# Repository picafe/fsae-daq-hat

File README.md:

# FSAE Pi HAT
## What this project is

This project is a revision 2.5 of the Raspberry Pi DAQ (data acquisition) HAT for Western Formula Racing FSAE. It consolidates the features still needed from the failed rev 2 boards into a single HAT: a 24 V → 5 V buck converter to power the Pi, input protection on the car rail, CAN transceiver + controller, static PoE injection control, and RTC with coin cell for the Pi 4B.

## Why I made it

A few months ago, I and another WFR team member tested and diagnosed a cause of catastrophic failure of the rev 2 DAQ HAT using voltage injection and a thermal camera. Although rev 3 was planned, and I am still working on it with help from others, the current failed rev 2 PCBs are still being partially used for their features that still function. This aims to be a quick revision that consolidates some of the features, while being cheap to manufacture. When revision 3 is finished, these boards can act as a backup.

The buck converter is one of the essential parts of the hat. Existing modules cut too many corners to be reliable, especially at 3A peak current. Currently, the buck coverter on the Rev 2 board is blown up. 

Rev 2 also included a boost converter to boost 20V USB-C PD to 24 V for injecting PoE for the base station antenna, and for ease of powering during testing. Since this is at a lower current, I decided to use a modified MT3608 boost converter and a PDC004 USB-C PD trigger on a separate PCB for ease of design and cost.

## Pictures

### 3D

### Schematic

**[View schematic online (KiCanvas)](https://kicanvas.org/?repo=https%3A%2F%2Fgithub.com%2Fpicafe%2Ffsae-daq-hat%2Fblob%2Fmain%2Ffsae-pihat%2Ffsae-pihat.kicad_sch)**

### PCB (KiCad)

**[View PCB online (KiCanvas)](https://kicanvas.org/?repo=https%3A%2F%2Fgithub.com%2Fpicafe%2Ffsae-daq-hat%2Fblob%2Fmain%2Ffsae-pihat%2Ffsae-pihat.kicad_pcb)**

### Wiring (off-board)

The 20 V USB-C PD → 24 V boost path is **not** on this HAT. It is implemented on the companion [USB boost/PD module](./fsae-pihat-usbmod/README.md), wired to the **J3** pads on the HAT.

```text
HAT J3 pads (no header installed)
    │  wire
    ▼
Deutsch connector
    │  wire
    ▼
USB-C PD breakout (MT3608 + PDC004)
```
The 2 main power devices source power from different sources using power OR-ing with schottky barrier diodes. 

The buck converter is powered by 24V from the car rail or the 20V USB-C PD (to reduce strain on the boost converter and to keep less ripple on the 5 V rail).
The PoE injector is powered by 24V from the car rail or the 24v boost converter.

A jumper on the **24 V car** input (JP2) can disable the car rail without unplugging the Deutsch connector, to preserve the car battery during bench testing. This MUST be populated to enable the car rail with a high current 0.1" pitch jumper. There is also a CAN termination jumper (JP1) to enable or disable 120Ω termination on the CAN bus.

## USB boost / PD module

The MT3608 boost and PDC004 USB-C PD trigger are on a separate PCB. Schematics, layout, images, and BOM for that board are in **[fsae-pihat-usbmod/README.md](./fsae-pihat-usbmod/README.md)**.

## Bill of materials (Pi HAT)

### JLCPCB SMT assembly

| Refs | Qty | Description | LCSC | Unit (USD) | Min | Ext. @ min (USD) |
| --- | ---: | --- | --- | ---: | ---: | ---: |
| C1, C2, C3 | 3 | 4.7 µF ±10% 50 V X7R ceramic, 1206 | [C29823](https://www.lcsc.com/product-detail/C29823.html) | $0.0426 | 10 | $0.43 |
| C10, C9 | 2 | 30 pF ±5% 50 V C0G ceramic, 0402 | [C1570](https://www.lcsc.com/product-detail/C1570.html) | $0.0013 | 100 | $0.13 |
| C11, C12 | 2 | 100 nF ±10% 50 V X7R ceramic, 0603 | [C14663](https://www.lcsc.com/product-detail/C14663.html) | $0.0031 | 100 | $0.31 |
| C4 | 1 | 10 nF ±10% 50 V X7R ceramic, 0805 | [C1710](https://www.lcsc.com/product-detail/C1710.html) | $0.0072 | 50 | $0.36 |
| C5 | 1 | 22 pF ±5% 50 V C0G ceramic, 0402 | [C1555](https://www.lcsc.com/product-detail/C1555.html) | $0.0014 | 100 | $0.14 |
| C6 | 1 | 330 µF ±20% 6.3 V tantalum, 7.3×4.3 mm SMD (6TPE330MAP) | [C79112](https://www.lcsc.com/product-detail/C79112.html) | $0.6851 | 1 | $0.69 |
| C7 | 1 | 100 nF ±10% 50 V X7R ceramic, 0402 | [C307331](https://www.lcsc.com/product-detail/C307331.html) | $0.0047 | 100 | $0.47 |
| C8 | 1 | 1 µF ±10% 25 V X5R ceramic, 0402 | [C52923](https://www.lcsc.com/product-detail/C52923.html) | $0.0040 | 100 | $0.40 |
| D1, D2, D4, D5 | 4 | 40 V 5 A Schottky, SMA (SS54) | [C7420369](https://www.lcsc.com/product-detail/C7420369.html) | $0.0448 | 10 | $0.45 |
| D10 | 1 | Emerald green 525 nm LED, 2.6–3.1 V, 0805 | [C2297](https://www.lcsc.com/product-detail/C2297.html) | $0.0163 | 50 | $0.82 |
| D11 | 1 | Red 630 nm LED, 1.6–2.6 V, 0805 | [C84256](https://www.lcsc.com/product-detail/C84256.html) | $0.0133 | 50 | $0.67 |
| D12 | 1 | Yellow 596 nm LED, 1.8–2.4 V, 0805 | [C2296](https://www.lcsc.com/product-detail/C2296.html) | $0.0122 | 50 | $0.61 |
| D3 | 1 | 40 V 5 A Schottky, SMC (SS54C) | [C18199188](https://www.lcsc.com/product-detail/C18199188.html) | $0.0737 | 10 | $0.74 |
| D6 | 1 | 64.5 V clamp TVS, 6.2 A Ipp, DO-214AC/SMA (SMAJ40CA) | — | — | — | — |
| D7, D9 | 2 | 40 V 30 mA Schottky, SOD-323 (RB751V-40) | [C7502691](https://www.lcsc.com/product-detail/C7502691.html) | $0.0149 | 50 | $0.75 |
| D8 | 1 | 50 V CAN TVS clamp, 5.5 A Ipp, SOT-23 (TPSM24CANB-02HTG) | [C970029](https://www.lcsc.com/product-detail/C970029.html) | $0.0495 | 10 | $0.50 |
| F1 | 1 | Polymeric PTC resettable fuse, 30 V 2 A, 1812 (1812L200/30GR) | [C18198342](https://www.lcsc.com/product-detail/C18198342.html) | $0.0812 | 5 | $0.41 |
| L1 | 1 | 15 µH ±20% shielded inductor, 5 A, 12.5×12.5 mm (SRR1260-150M) | [C2041333](https://www.lcsc.com/product-detail/C2041333.html) | $1.3721 | 1 | $1.37 |
| R1 | 1 | 1 kΩ ±5% resistor network, 0603×4 | [C20197](https://www.lcsc.com/product-detail/C20197.html) | $0.0059 | 50 | $0.30 |
| R10, R11, R12 | 3 | 4.7 kΩ ±1% thick-film, 0402 | [C25900](https://www.lcsc.com/product-detail/C25900.html) | $0.0010 | 100 | $0.10 |
| R13, R14, R19, R21, R4 | 5 | 10 kΩ ±1% thick-film, 0402 | [C25744](https://www.lcsc.com/product-detail/C25744.html) | $0.0013 | 100 | $0.13 |
| R15 | 1 | 680 Ω ±1% thick-film, 0402 | [C25130](https://www.lcsc.com/product-detail/C25130.html) | $0.0011 | 100 | $0.11 |
| R16, R18, R2, R3, R7, R8 | 6 | 470 Ω ±1% thick-film, 0402 | [C25117](https://www.lcsc.com/product-detail/C25117.html) | $0.0008 | 100 | $0.08 |
| R17 | 1 | 120 Ω ±1% thick-film, 0603 (CAN termination) | [C22787](https://www.lcsc.com/product-detail/C22787.html) | $0.0014 | 100 | $0.14 |
| R20 | 1 | 1 kΩ ±1% thick-film, 0603 | [C21190](https://www.lcsc.com/product-detail/C21190.html) | $0.0016 | 100 | $0.16 |
| R5 | 1 | 3 kΩ ±1% thick-film, 0603 | [C4211](https://www.lcsc.com/product-detail/C4211.html) | $0.0014 | 100 | $0.14 |
| R6 | 1 | 150 Ω ±1% thick-film, 0603 | [C22808](https://www.lcsc.com/product-detail/C22808.html) | $0.0018 | 100 | $0.18 |
| R9 | 1 | 1 kΩ ±1% thick-film, 0402 | [C11702](https://www.lcsc.com/product-detail/C11702.html) | $0.0011 | 100 | $0.11 |
| S1 | 1 | Tactile switch SPST, 160 gf, 4×3 mm SMD (TS-1088) | [C720477](https://www.lcsc.com/product-detail/C720477.html) | $0.0538 | 10 | $0.54 |
| U1 | 1 | TPS5430 buck regulator, 3 A, 5.5–36 V in, SOIC-8-EP | [C9864](https://www.lcsc.com/product-detail/C9864.html) | $0.7486 | 1 | $0.75 |
| U2 | 1 | TPS1H200A 2.5 A high-side switch (PoE injector), EMSOP-8-EP | [C2653785](https://www.lcsc.com/product-detail/C2653785.html) | $0.7476 | 1 | $0.75 |
| U3 | 1 | PCF8563T I²C real-time clock, SO-8 | [C7440](https://www.lcsc.com/product-detail/C7440.html) | $0.5834 | 1 | $0.58 |
| U4 | 1 | SN65HVD230 3.3 V CAN transceiver, 5 Mbps, SOP-8 | [C46596299](https://www.lcsc.com/product-detail/C46596299.html) | $0.4853 | 1 | $0.49 |
| U5 | 1 | MCP2515 1 Mbps CAN controller, TSSOP-20 | — | — | — | — |
| X1 | 1 | 32.768 kHz crystal ±20 ppm, 12.5 pF, SMD3215-2P | [C32346](https://www.lcsc.com/product-detail/C32346.html) | $0.1804 | 5 | $0.90 |
| X2 | 1 | 12 MHz crystal ±10 ppm, 20 pF, SMD3225-4P | [C9002](https://www.lcsc.com/product-detail/C9002.html) | $0.0744 | 10 | $0.74 |
| | | **LCSC subtotal @ MOQ** | | | | **$15.45 + 2 unlinked line items** |

### DigiKey (hand assembly)

| Refs | Qty | Description | DigiKey | Unit (CAD) | Ext. (CAD) |
| --- | ---: | --- | --- | ---: | ---: |
| J2 | 1 | 2×20 extended female GPIO header | [1568-16763-ND](https://www.digikey.ca/en/products/detail/sparkfun-electronics/16763/12686348) | $4.70 | $4.70 |
| J4, J5 | 2 | 4-pos 3.5 mm top-entry terminal block | [A123850-ND](https://www.digikey.ca/en/products/detail/te-connectivity-amp-connectors/1-2834011-4/5872966) | $1.57 | $3.14 |
| ETH1, ETH2 | 2 | RJ45 magjack 10/100 + PoE (Taoglas) | [931-TMJUTHQ0021192425-ND](https://www.digikey.ca/en/products/detail/taoglas-limited/TMJUTHQ0021192425/21777733) | $9.04 | $18.08 |
| FH1, FH2 | 2 | Blade fuse holder 30 A 500 V PCB | [36-3568-ND](https://www.digikey.ca/en/products/detail/keystone-electronics/3568/2137306) | $1.69 | $3.38 |
| BT1 | 1 | CR1225 coin-cell holder, 12 mm SMD | [BAT-HLD-012-SMTCT-ND](https://www.digikey.ca/en/products/detail/te-connectivity-linx/BAT-HLD-012-SMT-TR/5361776) | $0.75 | $0.75 |
| — | 1 | CR1225 3 V lithium cell (fits BT1) | *(Amazon, etc.)* | — | — |
| JP1, JP2 | 2 | 1×3 2.54 mm vertical pin header (solder to `JP1` / `JP2` footprints) | *(any 1×3 0.1″ 3A rated header)* | — | — |
| JP1 | 1 | CAN 120 Ω termination shunt | [S9341-ND](https://www.digikey.ca/en/products/detail/sullins-connector-solutions/NPC02SXON-RC/2618266) | $0.075 | $0.08 |
| JP2 | 1 | 24 V car-rail enable shunt | [S9341-ND](https://www.digikey.ca/en/products/detail/sullins-connector-solutions/NPC02SXON-RC/2618266) | $0.075 | $0.08 |
| | | **DigiKey subtotal (per board)** | | | **$30.20** |

**Not populated (DNP):**

| Refs | Footprint on PCB | Notes |
| --- | --- | --- |
| J1 | 2×2 pin socket | Do not install; car input harness wires solder to |
| J3 | 1×3 pin header | Do not install; boost/PD harness wires solder to |

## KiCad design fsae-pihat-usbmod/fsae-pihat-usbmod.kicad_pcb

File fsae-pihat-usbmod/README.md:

# FSAE Pi HAT USB Boost / PD Module

## What this project is

This PCB is the external **20 V USB-C PD → 24 V boost** module used with the [main Pi HAT](../README.md). It pairs a **PDC004 V2** USB-C PD trigger (fixed 20 V) with an **MT3608** boost module to generate 24 V for PoE injection on the base station antenna and for convenient bench power during testing. This is a companion PCB to the main Pi HAT.

## Why I made it

Since the current here would be pretty low, I decided to use a MT3608 and PDC004 PD module (I already have one, and the design seems pretty good; really big power plane on bottom) on a separate PCB instead of putting a boost converter on the HAT.

The MT3608 module also should be able to handle the current required (2 A) for the 24 V PoE injection, which should be around 1 A peak. The IC itself is pretty capable; there often just is not a great component selection or insufficient decoupling/filtering. I remembered [this GreatScott video](https://www.youtube.com/watch?v=6bicunweBAQ) where he added a 2.2 µF 1210 capacitor to the output of the MT3608 to improve output ripple, so I added **C1 (2.2 µF)**.

## Pictures

### Schematic

**[View schematic online (KiCanvas)](https://kicanvas.org/?repo=https%3A%2F%2Fgithub.com%2Fpicafe%2Ffsae-daq-hat%2Fblob%2Fmain%2Ffsae-pihat-usbmod%2Ffsae-pihat-usbmod.kicad_sch)**

### PCB

**[View PCB online (KiCanvas)](https://kicanvas.org/?repo=https%3A%2F%2Fgithub.com%2Fpicafe%2Ffsae-daq-hat%2Fblob%2Fmain%2Ffsae-pihat-usbmod%2Ffsae-pihat-usbmod.kicad_pcb)**

### Wiring (off-board)

Connect to the main HAT **J3** and a USB-C PD supply:

```text
USB-C PD supply (20 V negotiated)
    │
    ▼
PDC004 module (J2, bottom of this PCB) ──► +20 V rail
    │
    ▼
MT3608 boost (U1, top of this PCB) ──► +24 V
    │
    ▼
3-pin header J1 ──► wires ──► Deutsch connectors ──► main HAT J3
```

For the PCB, the PD module is surface mount on the bottom and the MT3608 on the top, since both have large pads on both sides with vias.

## Bill of materials

| Designator | Footprint / package | Qty | Value | Notes |
| --- | --- | ---: | --- | --- |
| J1 | PinSocket_1x03_P2.54mm_Vertical | 1 | Conn_01x03_Socket | To main HAT |
| J2 | PDC004 Module | 1 | PDC004 PD Trigger | Fixed 20 V USB-C PD; AliExpress module |
| U1 | MT3608 Module | 1 | MT3608 Boost | AliExpress / generic boost module |
| C1 | C_1210 (hand solder on module) | 1 | [2.2 µF, 50V X7R 1210 CL32B225KBJNNNE](https://www.digikey.ca/en/products/detail/samsung-electro-mechanics/CL32B225KBJNNNE/3888542) | Output stability cap; solder on MT3608 output  |

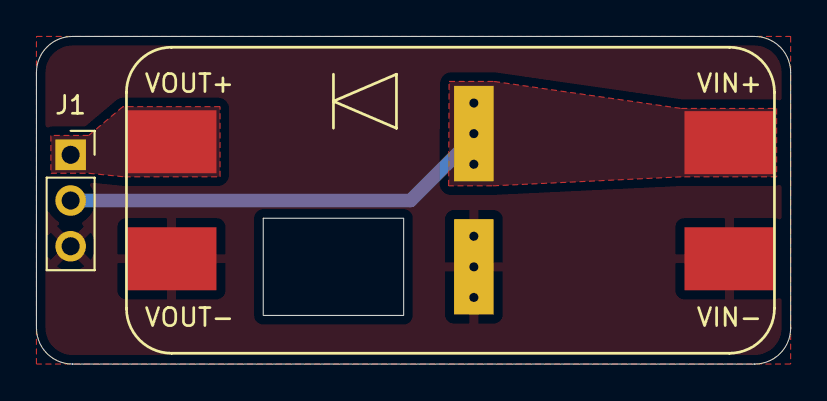
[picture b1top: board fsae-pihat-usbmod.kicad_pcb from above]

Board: 2 copper layers, 41.9 x 18.2 mm, 3 parts (1 on the bottom side), 3 nets.

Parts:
J1: Conn_01x03_Socket; PinSocket_1x03_P2.54mm_Vertical
J2: HUSB238 Module; HUSB238_module_purple
U1: MT3608 Boost; MT3608_module_SMT

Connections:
+20V: J1.2, J2.1 (OUT+), U1.1 (VIN+)
+24V: J1.1, U1.4 (VOUT-)
GND: J1.3, J2.2 (OUT-), U1.2 (VIN-), U1.3 (VOUT-)

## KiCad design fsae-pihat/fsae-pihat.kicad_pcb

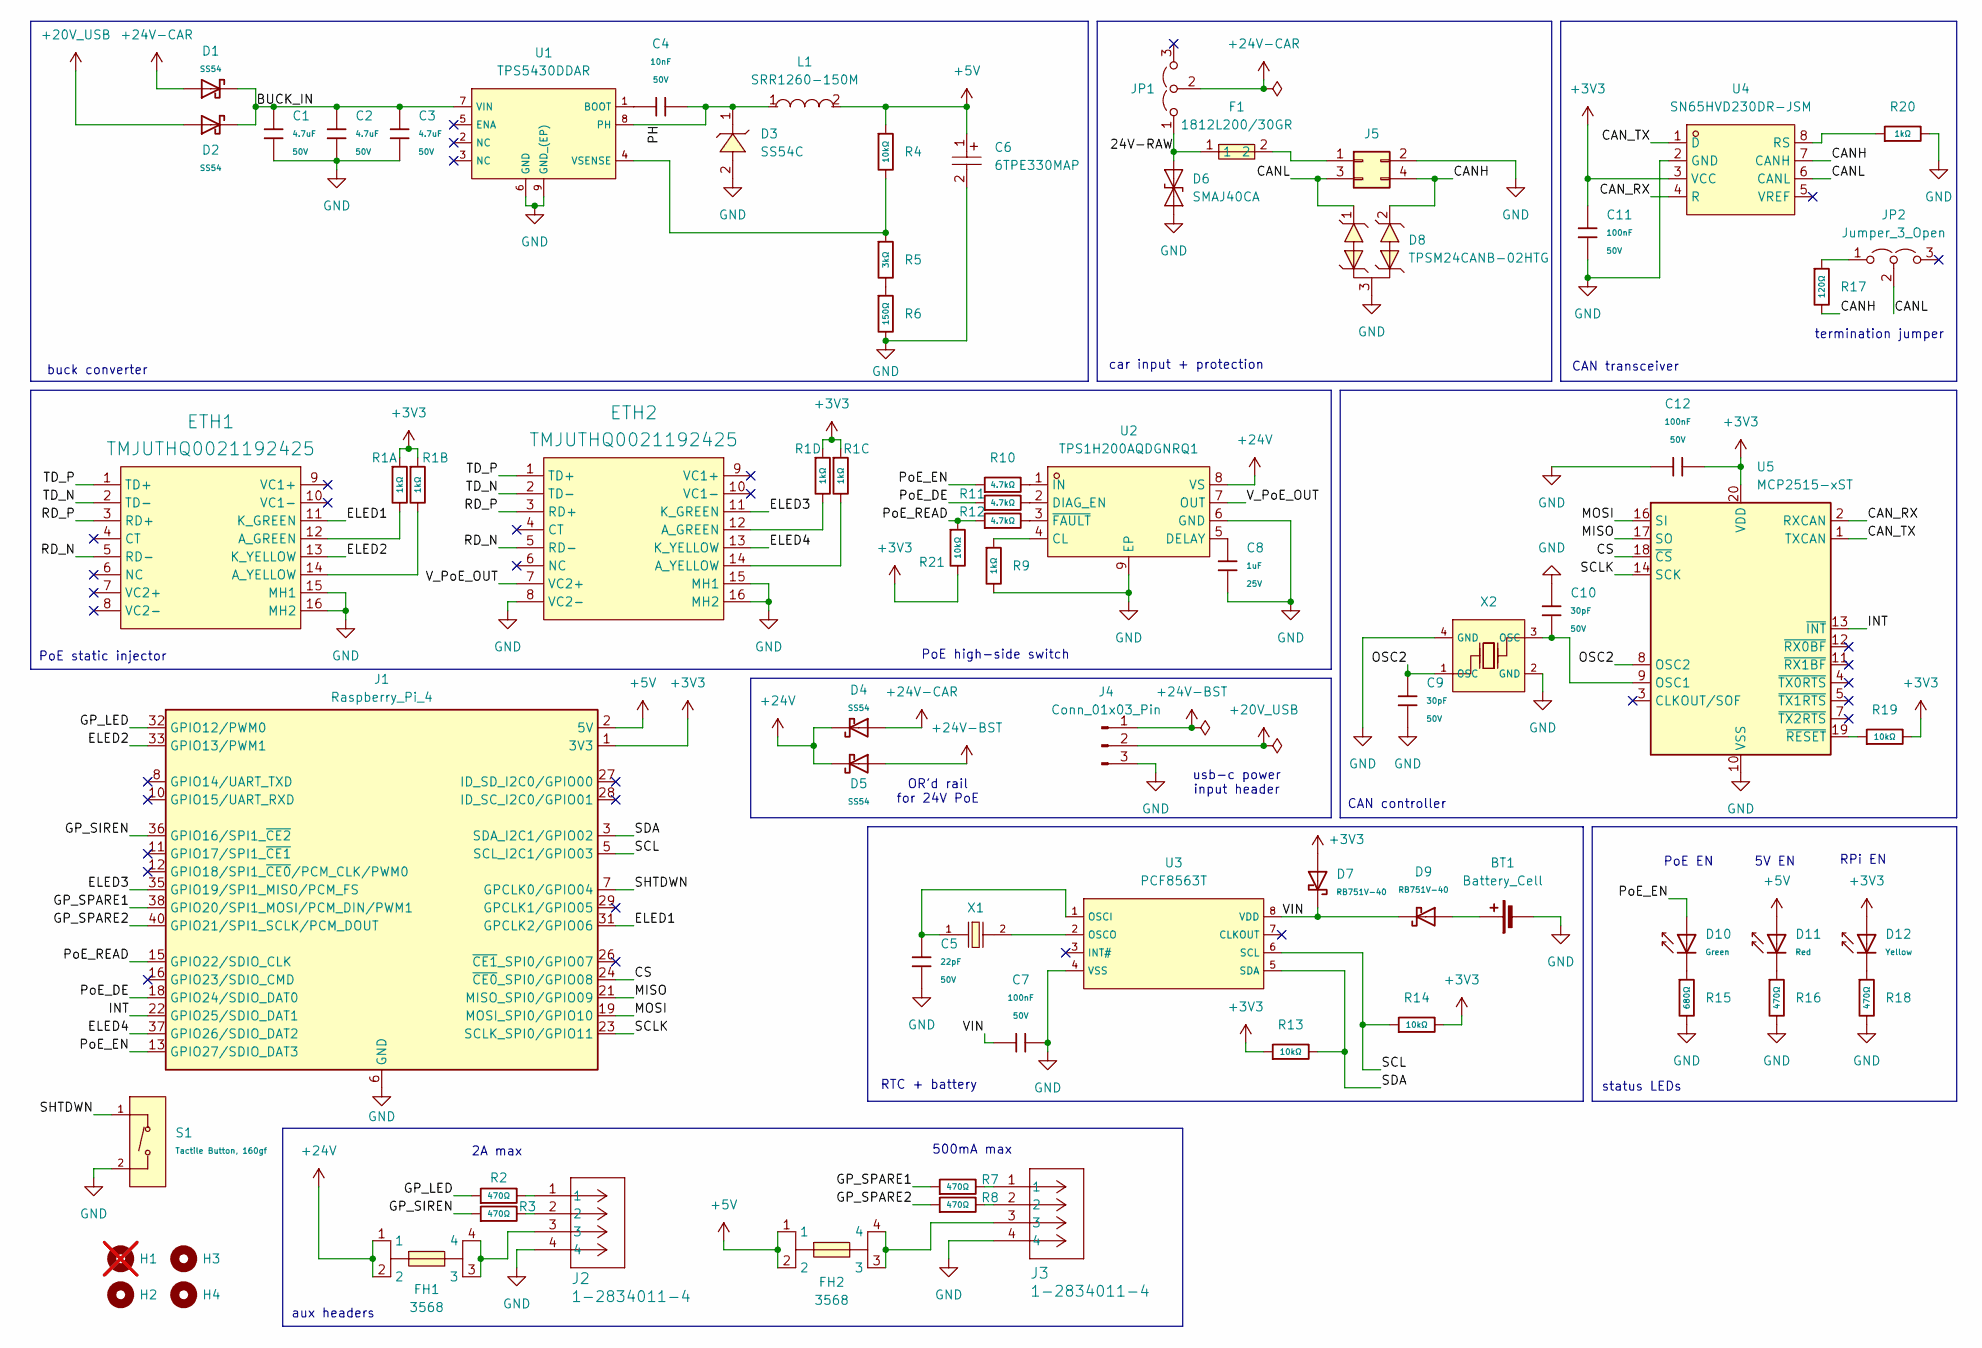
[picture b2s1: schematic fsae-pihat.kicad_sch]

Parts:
BT1: Battery_Cell; BAT-HLD-012-SMT-TR
C1, C2, C3: 4.7uF; C_1206; Voltage Rated 50V; Tolerance ±10%; Part 1206B475K500NT; LCSC C29823
C4: 10nF; C_0805; Voltage Rated 50V; Tolerance ±10%; Part CL21B103KBANNNC; LCSC C1710
C5: 22pF; C_0402; Voltage Rated 50V; Tolerance ±5%; Part 0402CG220J500NT; LCSC C1555
C6: 6TPE330MAP; CAP-SMD_L7.3-W4.3-R-RD; MPN 6TPE330MAP; LCSC Part C79112
C7: 100nF; C_0402; Voltage Rated 50V; Tolerance ±10%; Part CL05B104KB54PNC; LCSC C307331
C8: 1uF; C_0402; Voltage Rated 25V; Tolerance ±10%; Part CL05A105KA5NQNC; LCSC C52923
C9, C10: 30pF; C_0402; Voltage Rated 50V; Tolerance ±5%; Part 0402CG300J500NT; LCSC C1570
C11, C12: 100nF; C_0603; Voltage Rated 50V; Tolerance ±10%; Part CC0603KRX7R9BB104; LCSC C14663
D1, D2, D4, D5: SS54; D_SMA; Forward Voltage (Vf@If) 0.55V@5.0A; Reverse Voltage (Vr) 40V; Part SS54; LCSC C7420369
D3: SS54C; SMC_L6.9-W5.9-LS7.9-RD; MPN SS54C; LCSC Part C18199188
D6: SMAJ40CA; D_SMA
D7, D9: RB751V-40; D_SOD-323; Forward Voltage (Vf@If) 370mV@1mA; Reverse Voltage (Vr) 40V; Part RB751V-40; LCSC C7502691
D8: TPSM24CANB-02HTG; SOT-23-3_L2.9-W1.3-P1.90-LS2.4-BR; MPN TPSM24CANB-02HTG; LCSC Part C970029
D10: Green; D_0805; Part KT-0805G; LCSC C2297
D11: Red; D_0805; Forward Voltage (VF) 1.6V~2.6V; Part NCD0805R1; LCSC C84256
D12: Yellow; D_0805; Part KT-0805Y; LCSC C2296
ETH1, ETH2: TMJUTHQ0021192425; Manufacturer Part Number TMJUTHQ0021192425
F1: 1812L200/30GR; F1812; MPN 1812L200/30GR; LCSC Part C18198342
FH1, FH2: 3568; FUSE-SMD_4P-L16.0-W6.7-P3.40; MPN 3568; LCSC Part C5249699
H1: MountingHole; MountingHole_2.7mm_M2.5; not fitted
H2, H3, H4: MountingHole; MountingHole_2.7mm_M2.5
J1: Raspberry_Pi_4; PinSocket_2x20_P2.54mm_Vertical
J2, J3: 1-2834011-4; CONN_1-2834011-4_TEC
J4: Conn_01x03_Pin; PinSocket_1x03_P2.54mm_Vertical
J5: Conn_02x02_Odd_Even; PinSocket_2x02_P2.54mm_Vertical
JP1, JP2: Jumper_3_Open; PinHeader_1x03_P2.54mm_Vertical
L1: SRR1260-150M; IND-SMD_L12.5-W12.5_GSDRK127P; MPN SRR1260-150M; LCSC Part C2041333
R1: 1kΩ; R_0603x4; Tolerance ±5%; Part 4D03WGJ0102T5E; LCSC C20197
R2, R3, R7, R8, R16, R18: 470Ω; R_0402; Overload Voltage (Max) 50V; Tolerance ±1%; Part 0402WGF4700TCE; LCSC C25117
R4, R13, R14, R19, R21: 10kΩ; R_0402; Overload Voltage (Max) 50V; Tolerance ±1%; Part 0402WGF1002TCE; LCSC C25744
R5: 3kΩ; R_0603; Overload Voltage (Max) 75V; Tolerance ±1%; Part 0603WAF3001T5E; LCSC C4211
R6: 150Ω; R_0603; Overload Voltage (Max) 75V; Tolerance ±1%; Part 0603WAF1500T5E; LCSC C22808
R9: 1kΩ; R_0402; Overload Voltage (Max) 50V; Tolerance ±1%; Part 0402WGF1001TCE; LCSC C11702
R10, R11, R12: 4.7kΩ; R_0402; Overload Voltage (Max) 50V; Tolerance ±1%; Part 0402WGF4701TCE; LCSC C25900
R15: 680Ω; R_0402; Overload Voltage (Max) 50V; Tolerance ±1%; Part 0402WGF6800TCE; LCSC C25130
R17: 120Ω; R_0603; Overload Voltage (Max) 75V; Tolerance ±1%; Part 0603WAF1200T5E; LCSC C22787
R20: 1kΩ; R_0603; Overload Voltage (Max) 75V; Tolerance ±1%; Part 0603WAF1001T5E; LCSC C21190
S1: Tactile Button, 160gf; SW_SPST_TS-1088-xR020; Voltage Rating (Dc) 12V; Part TS-1088-AR02016; LCSC C720477
U1: TPS5430DDAR; ESOP-8_L4.9-W3.9-P1.27-LS6.0-TL-EP; Output Voltage 1.221V~32.04V; Input Voltage 5.5V~36V; Part TPS5430DDAR; LCSC C9864
U2: TPS1H200AQDGNRQ1; EMSOP-8_L3.0-W3.0-P0.65-LS4.9-BL-EP-A; MPN TPS1H200AQDGNRQ1; LCSC Part C2653785
U3: PCF8563T; SOIC-8_3.9x4.9mm_P1.27mm; Operating Voltage 1V~5.5V; Part PCF8563T/5,518; LCSC C7440
U4: SN65HVD230DR-JSM; SOP-8_3.9x4.9mm_P1.27mm; MPN SN65HVD230DR-JSM; LCSC Part C46596299
U5: MCP2515-xST; TSSOP-20_4.4x6.5mm_P0.65mm
X1: Q13FC1350000400; FC-135R_L3.2-W1.5; Frequency Tolerance ±20ppm; Part Q13FC13500004; LCSC C32346
X2: X322512MSB4SI; CRYSTAL-SMD_4P-L3.2-W2.5-BL; Frequency Tolerance ±10ppm; Part X322512MSB4SI; LCSC C9002

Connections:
+3V3: C11.1, C12.2, D7.2, D12.2, J1.1 (3V3), J1.17 (3V3), R1.1, R1.2, R1.3, R1.4, R13.1, R14.2, R19.2, R21.2, U4.3 (VCC), U5.20 (VDD)
+5V: C6.1, D11.2, FH2.1, FH2.2, J1.2 (5V), J1.4 (5V), L1.2, R4.1
+20V_USB: D2.2, J4.2
+24V: D4.1, D5.1, FH1.1, FH1.2, U2.8 (VS)
+24V-BST: D5.2, J4.1
+24V-CAR: D1.2, D4.2, JP1.2 (C)
/24V-RAW: D6.2 (A2), F1.1, JP1.1 (A)
/BUCK_IN: C1.1, C2.1, C3.1, D1.1, D2.1, U1.7 (VIN)
/CANH: D8.2, J5.4, R17.2, U4.7 (CANH)
/CANL: D8.1, J5.3, JP2.2 (C), U4.6 (CANL)
/CAN_RX: U4.4 (R), U5.2 (RXCAN)
/CAN_TX: U4.1 (D), U5.1 (TXCAN)
/CS: J1.24 (~CE0_SPI0/GPIO08), U5.18 (~CS)
/ELED1: ETH1.11 (K_GREEN), J1.31 (GPCLK2/GPIO06)
/ELED2: ETH1.13 (K_YELLOW), J1.33 (GPIO13/PWM1)
/ELED3: ETH2.11 (K_GREEN), J1.35 (GPIO19/SPI1_MISO/PCM_FS)
/ELED4: ETH2.13 (K_YELLOW), J1.37 (GPIO26/SDIO_DAT2)
/GP_LED: J1.32 (GPIO12/PWM0), R2.1
/GP_SIREN: J1.36 (GPIO16/SPI1_~CE2), R3.1
/GP_SPARE1: J1.38 (GPIO20/SPI1_MOSI/PCM_DIN/PWM1), R7.1
/GP_SPARE2: J1.40 (GPIO21/SPI1_SCLK/PCM_DOUT), R8.1
/INT: J1.22 (GPIO25/SDIO_DAT1), U5.13 (~INT)
/MISO: J1.21 (MISO_SPI0/GPIO09), U5.17 (SO)
/MOSI: J1.19 (MOSI_SPI0/GPIO10), U5.16 (SI)
/OSC2: C9.1, U5.8 (OSC2), X2.1 (OSC)
/PH: C4.2, D3.1, L1.1, U1.8 (PH)
/PoE_DE: J1.18 (GPIO24/SDIO_DAT0), R11.1
/PoE_EN: D10.2, J1.13 (GPIO27/SDIO_DAT3), R10.1
/PoE_READ: J1.15 (GPIO22/SDIO_CLK), R12.1, R21.1
/RD_N: ETH1.5 (RD-), ETH2.5 (RD-)
/RD_P: ETH1.3 (RD+), ETH2.3 (RD+)
/SCL: J1.5 (SCL_I2C1/GPIO03), R14.1, U3.6 (SCL)
/SCLK: J1.23 (SCLK_SPI0/GPIO11), U5.14 (SCK)
/SDA: J1.3 (SDA_I2C1/GPIO02), R13.2, U3.5 (SDA)
/SHTDWN: J1.7 (GPCLK0/GPIO04), S1.1 (A)
/TD_N: ETH1.2 (TD-), ETH2.2 (TD-)
/TD_P: ETH1.1 (TD+), ETH2.1 (TD+)
/VIN: C7.1, D7.1, D9.1, U3.8 (VDD)
/V_PoE_OUT: ETH2.7 (VC2+), U2.7 (OUT)
GND: BT1.2 (-), C1.2, C2.2, C3.2, C5.2, C6.2, C7.2, C8.2, C9.2, C10.1, C11.2, C12.1, D3.2, D6.1 (A1), D8.3, ETH1.15 (MH1), ETH1.16 (MH2), ETH2.8 (VC2-), ETH2.15 (MH1), ETH2.16 (MH2), J1.6 (GND), J1.9 (GND), J1.14 (GND), J1.20 (GND), J1.25 (GND), J1.30 (GND), J1.34 (GND), J1.39 (GND), J2.4, J3.4, J4.3, J5.2, R6.2, R9.2, R15.2, R16.2, R18.2, R20.2, S1.2 (B), U1.6 (GND), U1.9 (GND_(EP)), U2.6 (GND), U2.9 (EP), U3.4 (VSS), U4.2 (GND), U5.10 (VSS), X2.2 (GND), X2.4 (GND)
unnamed: BT1.1 (+), D9.2
unnamed: D10.1, R15.1
unnamed: D11.1, R16.1
unnamed: D12.1, R18.1
unnamed: ETH1.12 (A_GREEN), R1.8
unnamed: ETH1.14 (A_YELLOW), R1.7
unnamed: ETH2.12 (A_GREEN), R1.5
unnamed: ETH2.14 (A_YELLOW), R1.6
unnamed: FH1.3, FH1.4, J2.3
unnamed: FH2.3, FH2.4, J3.3
unnamed: J2.1, R2.2
unnamed: J2.2, R3.2
unnamed: J3.1, R7.2
unnamed: J3.2, R8.2
unnamed: F1.2, J5.1
unnamed: JP2.1 (A), R17.1
unnamed: R5.2, R6.1
unnamed: C4.1, U1.1 (BOOT)
unnamed: R4.2, R5.1, U1.4 (VSENSE)
unnamed: R9.1, U2.4 (CL)
unnamed: C8.1, U2.5 (DELAY)
unnamed: R11.2, U2.2 (DIAG_EN)
unnamed: R10.2, U2.1 (IN)
unnamed: R12.2, U2.3 (~FAULT)
unnamed: C5.1, U3.1 (OSCI), X1.1
unnamed: U3.2 (OSCO), X1.2
unnamed: R20.1, U4.8 (RS)
unnamed: C10.2, U5.9 (OSC1), X2.3 (OSC)
unnamed: R19.1, U5.19 (~RESET)

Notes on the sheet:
buck converter
aux headers
RPi EN
2A max
5V EN
PoE EN
500mA max
car input + protection
PoE high-side switch
usb-c power input header
CAN transceiver
status LEDs
termination jumper
PoE static injector
CAN controller
OR'd rail for 24V PoE
RTC + battery

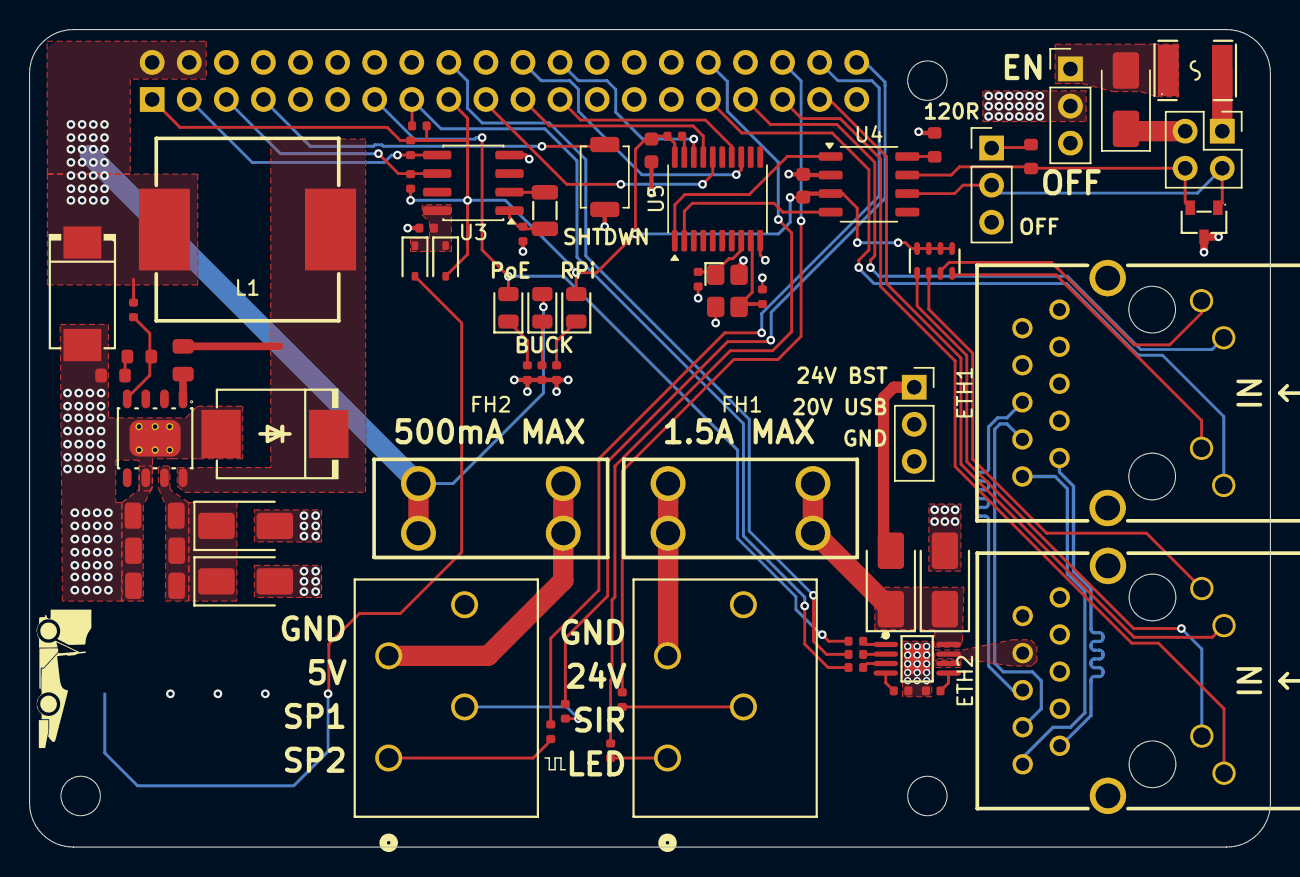
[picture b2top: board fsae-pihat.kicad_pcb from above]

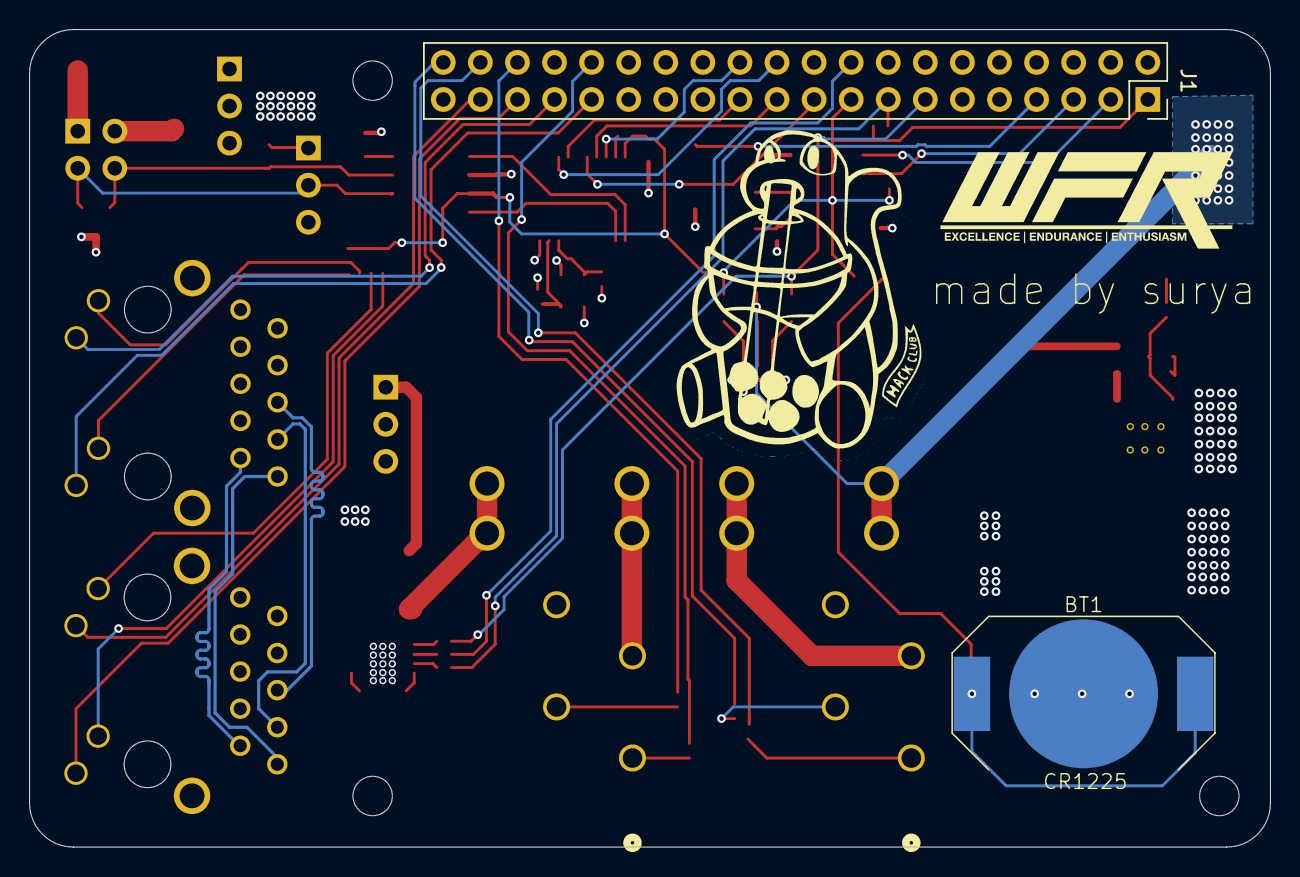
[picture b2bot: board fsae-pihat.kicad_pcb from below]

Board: 4 copper layers, 85.0 x 56.0 mm, 70 parts (2 on the bottom side), 69 nets.

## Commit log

2026-05-21 init
2026-05-22 feat: readme, journal, pcb updates
2026-05-22 fix: readme details
2026-05-23 feat: documentation and assembly
2026-05-23 fix: assembly
2026-05-23 fix: readme
2026-05-27 feat: pcb art and updated design
2026-05-28 fix: missed hat pullup; feat: new pd module
2026-05-28 feat: update journal
2026-05-28 fix: usb module fp + pcb
